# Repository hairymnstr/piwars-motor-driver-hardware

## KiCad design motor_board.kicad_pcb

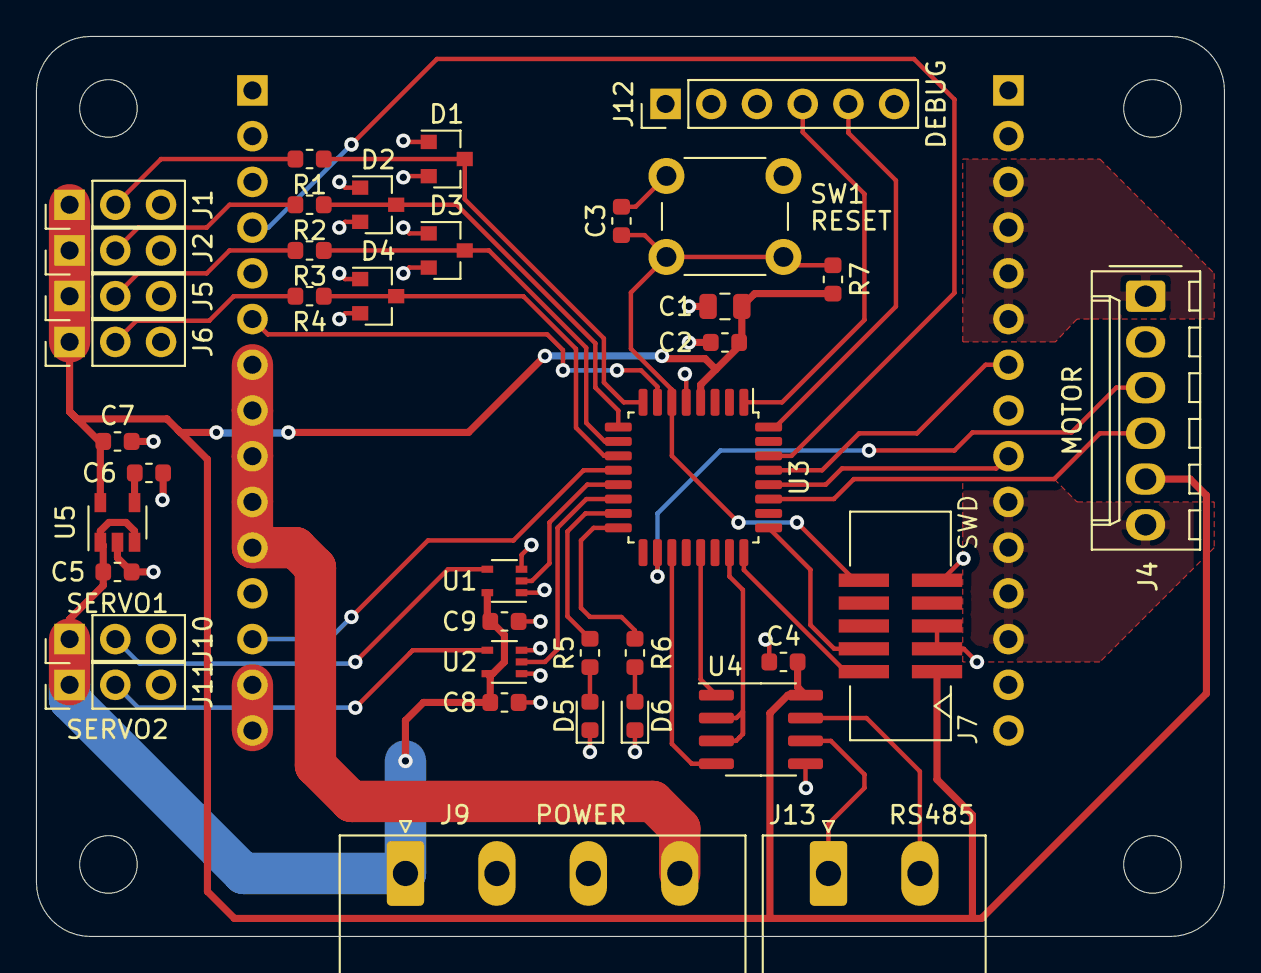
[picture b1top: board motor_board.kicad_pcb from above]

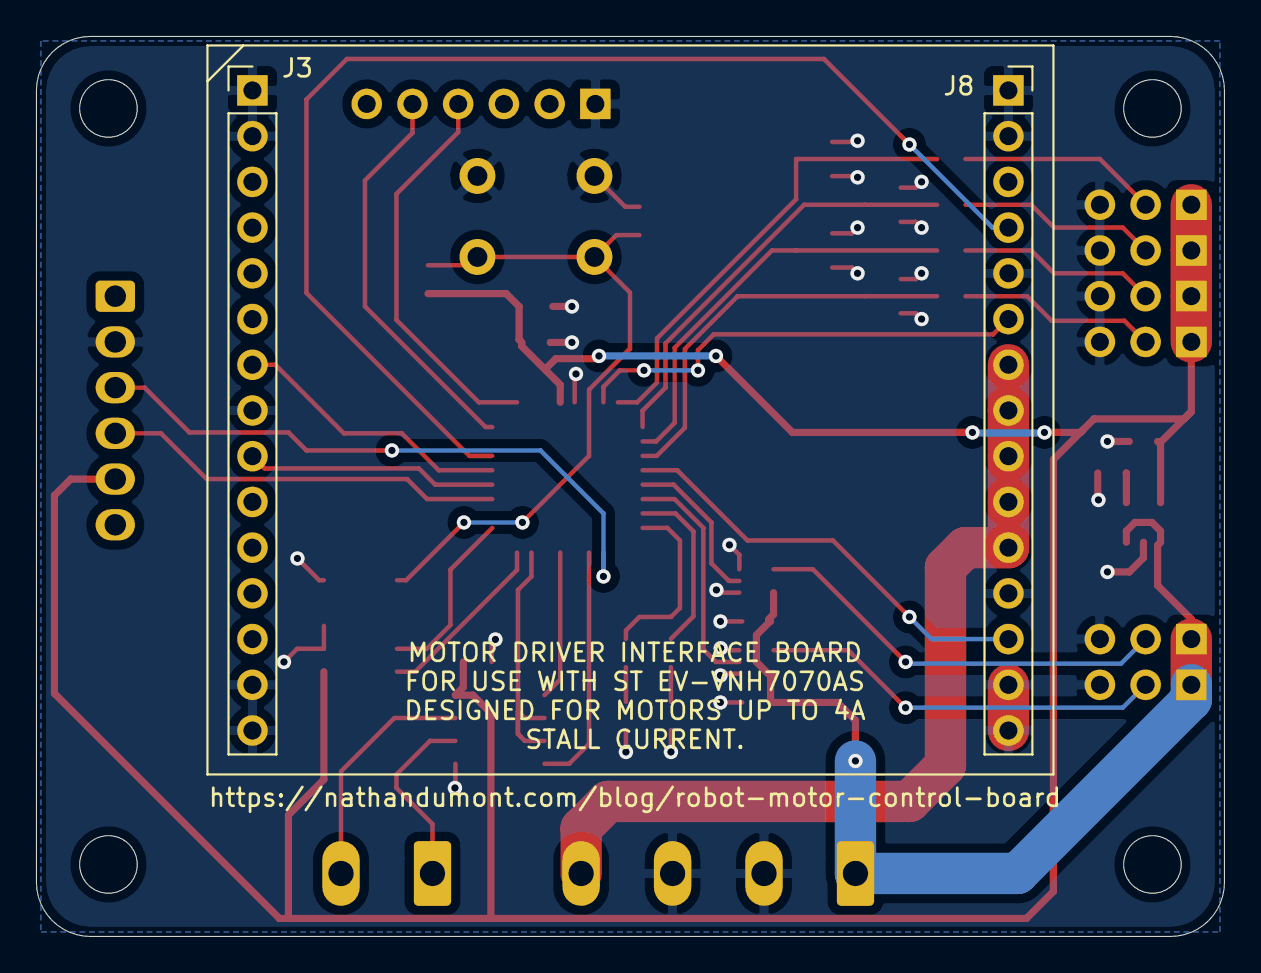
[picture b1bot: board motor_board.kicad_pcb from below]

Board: 2 copper layers, 66.0 x 50.0 mm, 45 parts (2 on the bottom side), 40 nets.

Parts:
C1: 4.7µF; C_0805_2012Metric
C2, C3, C4, C8, C9: 100nF; C_0603_1608Metric
C5, C7: 1µF; C_0603_1608Metric
C6: 10nF; C_0603_1608Metric
D1, D2, D3, D4: D_TVS_AAK; SOT-23
D5: LED0; LED_0603_1608Metric
D6: LED1; LED_0603_1608Metric
H1, H2, H3, H4: MountingHole; MountingHole_3.2mm_M3
J1: AUX1; PinHeader_1x03_P2.54mm_Vertical
J2: AUX2; PinHeader_1x03_P2.54mm_Vertical
J3: Conn_01x15; PinHeader_1x15_P2.54mm_Vertical
J4: MOTOR; Molex_KK-254_AE-6410-06A_1x06_P2.54mm_Vertical
J5: AUX3; PinHeader_1x03_P2.54mm_Vertical
J6: AUX4; PinHeader_1x03_P2.54mm_Vertical
J7: SWD; SAMTEC_SHF-SM_5x2
J8: Conn_01x15; PinSocket_1x15_P2.54mm_Vertical
J9: POWER; PhoenixContact_MSTBA_2,5_4-G-5,08_1x04_P5.08mm_Horizontal
J10: SERVO1; PinHeader_1x03_P2.54mm_Vertical
J11: SERVO2; PinHeader_1x03_P2.54mm_Vertical
J12: DEBUG; PinHeader_1x06_P2.54mm_Vertical
J13: RS485; PhoenixContact_MSTBA_2,5_2-G-5,08_1x02_P5.08mm_Horizontal
R1, R2, R3, R4: 1kΩ; R_0603_1608Metric
R5, R6: 330Ω; R_0603_1608Metric
R7: 10kΩ; R_0603_1608Metric
SW1: RESET; SW_PUSH_6mm
U1, U2: 74AHCT1G125; SOT-353_SC-70-5
U3: STM32G071KxT; LQFP-32_7x7mm_P0.8mm
U4: MAX3485; SOIC-8_3.9x4.9mm_P1.27mm
U5: LDK130-33_SOT23_SOT353; SOT-23-5

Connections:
+3V3: C1.2, C2.2, C4.2, C7.1, J1.1, J2.1, J4.5, J5.1, J6.1, J7.1, R7.1, U3.4, U4.8, U5.5
+5V: C5.1, C8.2, C9.2, J9.1, J10.1, J11.1, U1.5, U2.5, U5.1, U5.3
+12V: J8.7, J8.8, J8.9, J8.10, J8.11, J9.4
/AUX1: D1.3, R1.1, U3.8
/AUX2: D2.3, R2.1, U3.9
/AUX3: D3.3, R3.1, U3.10
/AUX4: D4.3, R4.1, U3.11
/CUR_SENS: J8.6, U3.7
/DIRA: J3.7, U3.29
/DIRB: J3.9, U3.28
/ENC_A: J4.3, U3.18
/ENC_B: J4.4, U3.27
/MOTOR_N: J3.10, J3.11, J3.12, J3.13, J4.6
/MOTOR_P: J3.3, J3.4, J3.5, J3.6, J4.1
/RS485_DE: U3.23, U4.2, U4.3
/RS485_RX: U3.21, U4.1
/RS485_TX: U3.19, U4.4
/SEL0: J8.4, U3.30
/SERVO1: U1.2, U3.13
/SERVO2: U2.2, U3.14
/SRST: C3.1, J7.10, R7.2, SW1.1, U3.6
/SWCLK: J7.4, U3.25
/SWDIO: J7.2, U3.24
/TIM2_CH1: J8.13, U3.12
/USART3_RX: J12.4, U3.1
/USART3_TX: J12.5, U3.32
GND: C1.1, C2.1, C3.2, C4.1, C5.2, C6.2, C7.2, C8.1, C9.1, D1.1, D1.2, D2.1, D2.2, D3.1, D3.2, D4.1, D4.2, D5.1, D6.1, J1.3, J2.3, J3.1, J3.2, J3.8, J3.14, J3.15, J4.2, J5.3, J6.3, J7.3, J7.5, J7.9, J8.1, J8.2, J8.5, J8.12, J8.14, J8.15, J9.2, J9.3, J10.3, J11.3, J12.1, SW1.2, U1.1, U1.3, U2.1, U2.3, U3.5, U4.5, U5.2
unnamed: C6.1, U5.4
unnamed: D5.2, R5.1
unnamed: D6.2, R6.1
unnamed: J1.2, R1.2
unnamed: J2.2, R2.2
unnamed: J5.2, R3.2
unnamed: J6.2, R4.2
unnamed: J10.2, U1.4
unnamed: J11.2, U2.4
unnamed: J13.1, U4.6
unnamed: J13.2, U4.7
unnamed: R5.2, U3.15
unnamed: R6.2, U3.16

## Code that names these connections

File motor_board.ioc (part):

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Mcu.UserName=STM32G071KBTx
PA12\ [PA10].Mode=Hardware Flow Control (RS485)
PA14-BOOT0.Mode=Serial_Wire
PB0.GPIO_Label=LED0
PB6.GPIO_Label=SEL0
RCC.SYSCLKSource=RCC_SYSCLKSOURCE_PLLCLK
PB5.GPIOParameters=GPIO_Label
PB4.GPIOParameters=GPIO_Label
PA4.Mode=IN4
PA12\ [PA10].Signal=USART1_DE
PB6.Signal=GPIO_Output
PA14-BOOT0.Signal=SYS_SWCLK
RCC.HSE_VALUE=8000000
PB0.GPIOParameters=GPIO_Label
PB1.GPIO_Label=LED1
PA0.Mode=IN0
PA8.Signal=S_TIM1_CH1
PB6.GPIOParameters=GPIO_Label
PA0.Signal=ADC1_IN0
Mcu.Package=LQFP32
PB9.Signal=USART3_RX
PB1.Signal=GPIO_Output
PA6.Signal=S_TIM3_CH1
PA10.Signal=USART1_RX
PB5.GPIO_Label=DIRB
PB4.Signal=GPIO_Output
PA3.Signal=ADC1_IN3
PA10.Mode=Asynchronous
PA13.Signal=SYS_SWDIO
PA3.Mode=IN3
PA9.Mode=Asynchronous
PB9.Mode=Asynchronous
PA9.Signal=USART1_TX
PA1.Signal=ADC1_IN1
PA5.Signal=S_TIM2_CH1
board=custom
PA1.Mode=IN1
PB4.GPIO_Label=DIRA
PA13.Mode=Serial_Wire
Mcu.Name=STM32G071K(6-8-B)Tx
PA2.Signal=ADC1_IN2
PB3.Signal=S_TIM1_CH2
PA4.Signal=ADC1_IN4
RCC.SYSCLKFreq_VALUE=64000000
PB5.Signal=GPIO_Output
PB8.Mode=Asynchronous
PB8.Signal=USART3_TX
PA2.Mode=IN2
PB0.Signal=GPIO_Output
PB1.GPIOParameters=GPIO_Label
PA7.Signal=S_TIM3_CH2

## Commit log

2022-02-17 Finally preparing to push to github
2022-02-17 Updated to KiCad 6
2022-02-17 Excluded the new KiCad 6 backups folder
2022-02-17 Added a readme with some brief details
